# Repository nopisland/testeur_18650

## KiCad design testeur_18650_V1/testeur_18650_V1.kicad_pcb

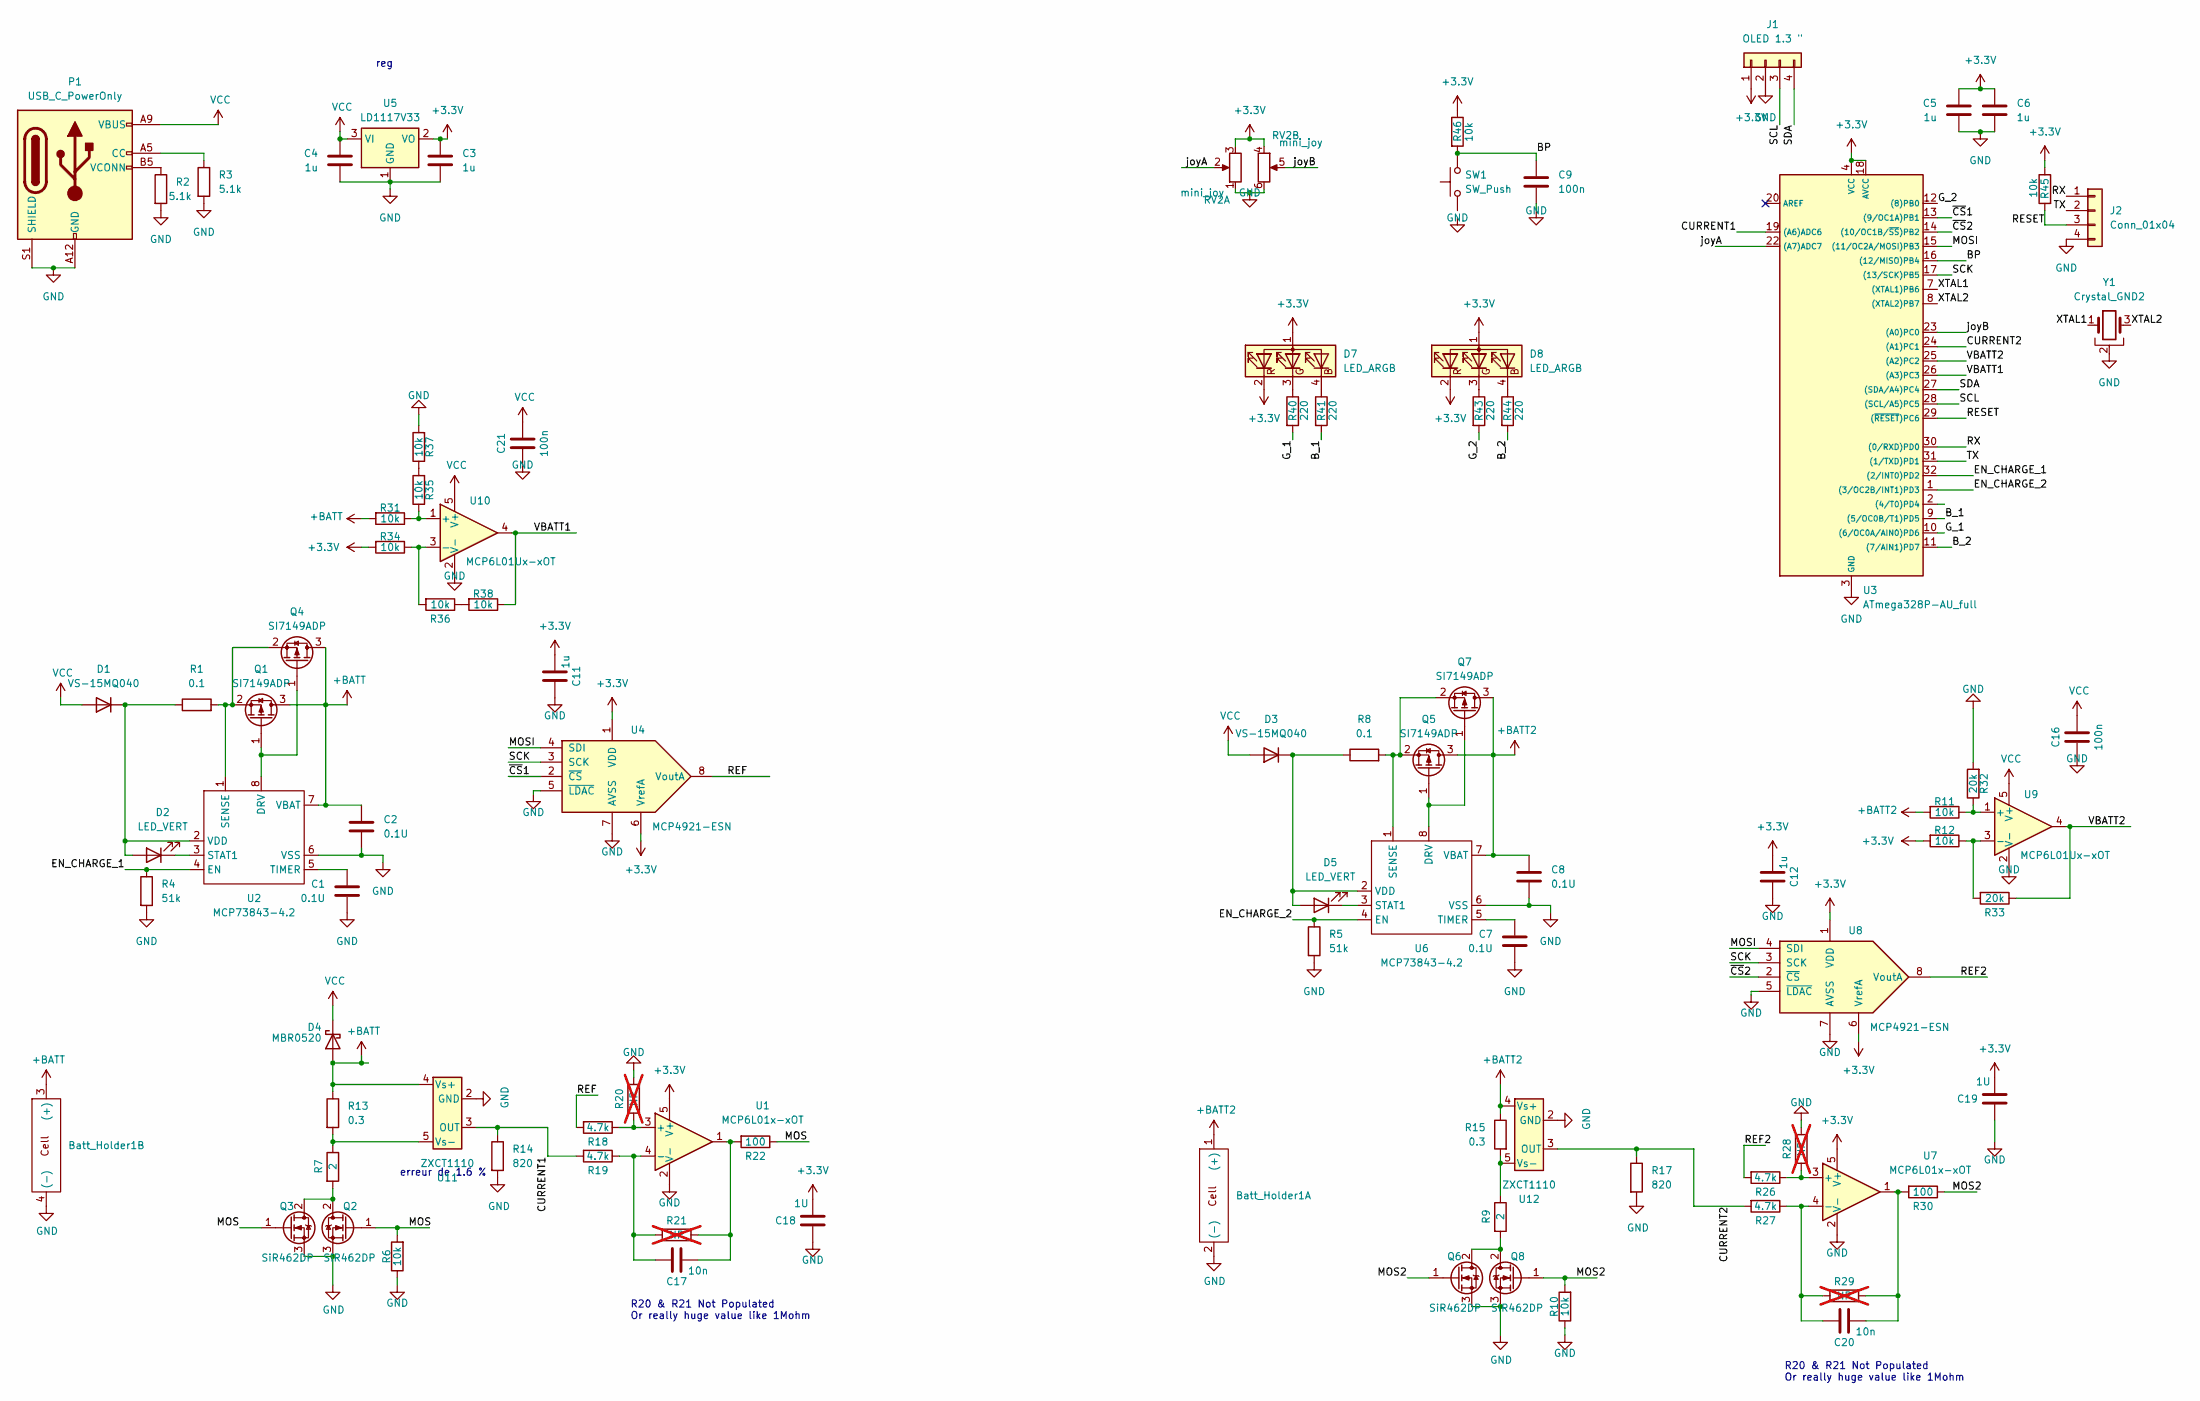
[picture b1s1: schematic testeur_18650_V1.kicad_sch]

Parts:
Batt_Holder1: Cell_holder_18650_2
C1, C2, C7, C8: 0.1U; C_0603_1608Metric
C3, C4, C5, C6, C11, C12: 1u; C_0603_1608Metric
C9, C16, C21: 100n; C_0603_1608Metric
C17, C20: 10n; C_0603_1608Metric
C18, C19: 1U; C_0603_1608Metric
D1, D3: VS-15MQ040; D_SMA
D2, D5: LED_VERT; LED_0603_1608Metric
D4: MBR0520; D_SOD-123
D7, D8: LED_ARGB; LED_ASMB-KTF0-0A306
J1: OLED 1.3 "; OLED_1.3inch
J2: Conn_01x04; PinHeader_1x04_P2.54mm_Vertical
P1: USB_C_PowerOnly; USB_C_Receptacle_GCT_USB4135-GF-A_6P_TopMnt_Horizontal
Q1, Q4, Q5, Q7: SI7149ADP; PowerPAK_SO8L
Q2, Q3, Q6, Q8: SiR462DP; PowerPAK_SO8L
R1, R8: 0.1; R_1206_3216Metric
R2, R3: 5.1k; R_0603_1608Metric
R4, R5: 51k; R_0603_1608Metric
R6, R10, R11, R12, R31, R34, R35, R36, R37, R38, R45, R46: 10k; R_0603_1608Metric
R7, R9: 2; Resistor_RH25
R13, R15: 0.3; R_1206_3216Metric
R14, R17: 820; R_0603_1608Metric
R18, R19, R26, R27: 4.7k; R_0603_1608Metric
R20, R21, R28, R29: NP; R_0603_1608Metric; not fitted
R22, R30: 100; R_0603_1608Metric
R32, R33: 20k; R_0603_1608Metric
R40, R41, R43, R44: 220; R_0603_1608Metric
RV2: mini_joy; mini_joy_analog
SW1: SW_Push; BP_Schruter_LSH
U1, U7: MCP6L01x-xOT; SOT-23-5
U2, U6: MCP73843-4.2; MSOP-8_3x3mm_P0.65mm
U3: ATmega328P-AU_full; TQFP32m
U4, U8: MCP4921-ESN; MSOP-8_3x3mm_P0.65mm
U5: LD1117V33; SOT-223-3_TabPin2
U9, U10: MCP6L01Ux-xOT; SOT-23-5
U11, U12: ZXCT1110; SOT-23-5
Y1: Crystal_GND2; osc_CSTNE

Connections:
+3.3V: C3.1, C5.1, C6.1, C11.1, C12.1, C18.1, C19.1, D7.1 (A), D7.2 (RK), D8.1 (A), D8.2 (RK), J1.1, R12.2, R34.2, R45.1, R46.1, RV2.3, RV2.4, U1.5 (V+), U3.4 (VCC), U3.6 (VCC), U3.18 (AVCC), U4.1 (VDD), U4.6 (VrefA), U5.2 (VO), U7.5 (V+), U8.1 (VDD), U8.6 (VrefA)
+BATT: Batt_Holder1.3 ((+)), C2.1, D4.2 (A), Q1.3 (D), Q4.3 (D), R13.1, R31.2, U2.7 (VBAT), U11.4 (Vs+)
+BATT2: Batt_Holder1.1 ((+)), C8.1, Q5.3 (D), Q7.3 (D), R11.2, R15.1, U6.7 (VBAT), U12.4 (Vs+)
/BP: C9.1, R46.2, SW1.2 (2_2), U3.16 ((12/MISO)PB4)
/B_1: R41.2, U3.9 ((5/OC0B/T1)PD5)
/B_2: R44.2, U3.11 ((7/AIN1)PD7)
/CURRENT1: R14.1, R19.2, U3.19 ((A6)ADC6), U11.3 (OUT)
/CURRENT2: R17.1, R27.2, U3.24 ((A1)PC1), U12.3 (OUT)
/EN_CHARGE_1: R4.1, U2.4 (EN), U3.32 ((2/INT0)PD2)
/EN_CHARGE_2: R5.1, U3.1 ((3/OC2B/INT1)PD3), U6.4 (EN)
/G_1: R40.2, U3.10 ((6/OC0A/AIN0)PD6)
/G_2: R43.2, U3.12 ((8)PB0)
/MOS: Q2.1 (G), Q3.1 (G), R6.2, R22.1
/MOS2: Q6.1 (G), Q8.1 (G), R10.2, R30.1
/MOSI: U3.15 ((11/OC2A/MOSI)PB3), U4.4 (SDI), U8.4 (SDI)
/REF: R18.2, U4.8 (VoutA)
/REF2: R26.2, U8.8 (VoutA)
/RESET: J2.3, R45.2, U3.29 ((~RESET)PC6)
/RX: J2.1, U3.30 ((0/RXD)PD0)
/SCK: U3.17 ((13/SCK)PB5), U4.3 (SCK), U8.3 (SCK)
/SCL: J1.3, U3.28 ((SCL/A5)PC5)
/SDA: J1.4, U3.27 ((SDA/A4)PC4)
/TX: J2.2, U3.31 ((1/TXD)PD1)
/VBATT1: R38.1, U3.26 ((A3)PC3), U10.4
/VBATT2: R33.1, U3.25 ((A2)PC2), U9.4
/XTAL1: U3.7 ((XTAL1)PB6), Y1.1
/XTAL2: U3.8 ((XTAL2)PB7), Y1.3
/joyA: RV2.2, U3.22 ((A7)ADC7)
/joyB: RV2.5, U3.23 ((A0)PC0)
/~CS1: U3.13 ((9/OC1A)PB1), U4.2 (~CS)
/~CS2: U3.14 ((10/OC1B/~SS)PB2), U8.2 (~CS)
GND: Batt_Holder1.2 ((-)), Batt_Holder1.4 ((-)), C1.2, C2.2, C3.2, C4.2, C5.2, C6.2, C7.2, C8.2, C9.2, C11.2, C12.2, C16.1, C18.2, C19.2, C21.1, J1.2, J2.4, P1.A12 (GND), P1.B12 (GND), P1.S1 (SHIELD), Q2.3 (S), Q3.3 (S), Q6.3 (S), Q8.3 (S), R2.2, R3.2, R4.2, R5.2, R6.1, R10.1, R14.2, R17.2, R20.2, R28.2, R32.2, R37.2, RV2.1, RV2.6, U1.2 (V-), U2.6 (VSS), U3.3 (GND), U3.5 (GND), U3.21 (GND), U4.5 (~LDAC), U4.7 (AVSS), U5.1 (GND), U6.6 (VSS), U7.2 (V-), U8.5 (~LDAC), U8.7 (AVSS), U9.2 (V-), U10.2 (V-), U11.2 (GND), U12.2 (GND), Y1.2
unnamed: C17.1, R21.2, R22.2, U1.1
unnamed: C20.1, R29.2, R30.2, U7.1
unnamed: D1.1 (K), D2.2 (A), R1.1, U2.2 (VDD)
unnamed: D2.1 (K), U2.3 (STAT1)
unnamed: D3.1 (K), D5.2 (A), R8.1, U6.2 (VDD)
unnamed: D5.1 (K), U6.3 (STAT1)
unnamed: D7.4 (BK), R41.1
unnamed: D7.3 (GK), R40.1
unnamed: D8.4 (BK), R44.1
unnamed: D8.3 (GK), R43.1
unnamed: P1.A5 (CC), R3.1
unnamed: P1.B5 (VCONN), R2.1
unnamed: Q1.1 (G), Q4.1 (G), U2.8 (DRV)
unnamed: Q1.2 (S), Q4.2 (S), R1.2, U2.1 (SENSE)
unnamed: Q2.2 (D), Q3.2 (D), R7.2
unnamed: Q5.1 (G), Q7.1 (G), U6.8 (DRV)
unnamed: Q5.2 (S), Q7.2 (S), R8.2, U6.1 (SENSE)
unnamed: Q6.2 (D), Q8.2 (D), R9.2
unnamed: R35.2, R37.1
unnamed: R36.1, R38.2
unnamed: R18.1, R20.1, U1.3 (+)
unnamed: C17.2, R19.1, R21.1, U1.4 (-)
unnamed: C1.1, U2.5 (TIMER)
unnamed: C7.1, U6.5 (TIMER)
unnamed: R26.1, R28.1, U7.3 (+)
unnamed: C20.2, R27.1, R29.1, U7.4 (-)
unnamed: R11.1, R32.1, U9.1 (+)
unnamed: R12.1, R33.2, U9.3 (-)
unnamed: R31.1, R35.1, U10.1 (+)
unnamed: R34.1, R36.2, U10.3 (-)
unnamed: R7.1, R13.2, U11.5 (Vs-)
unnamed: R9.1, R15.2, U12.5 (Vs-)
VCC: C4.1, C16.2, C21.2, D1.2 (A), D3.2 (A), D4.1 (K), P1.A9 (VBUS), P1.B9 (VBUS), U5.3 (VI), U9.5 (V+), U10.5 (V+)

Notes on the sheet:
R20 & R21 Not Populated Or really huge value like 1Mohm
erreur de 1.6 %
reg

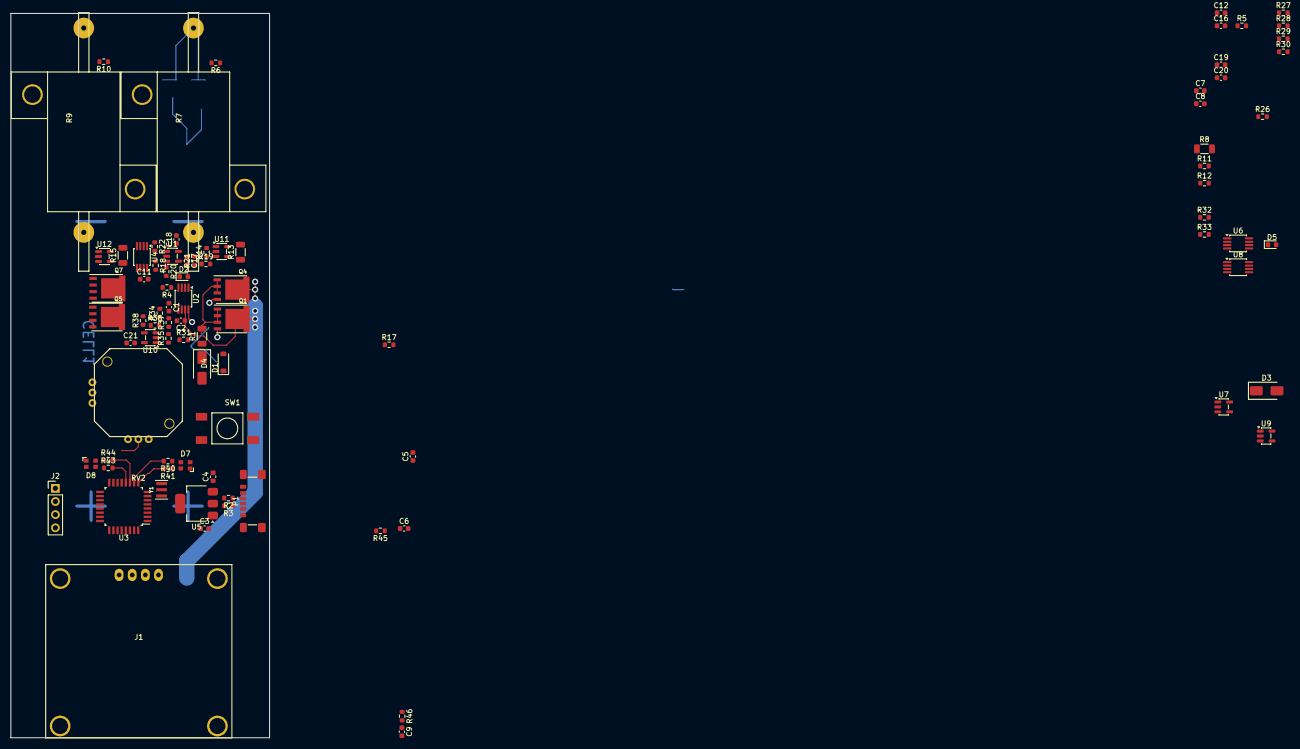
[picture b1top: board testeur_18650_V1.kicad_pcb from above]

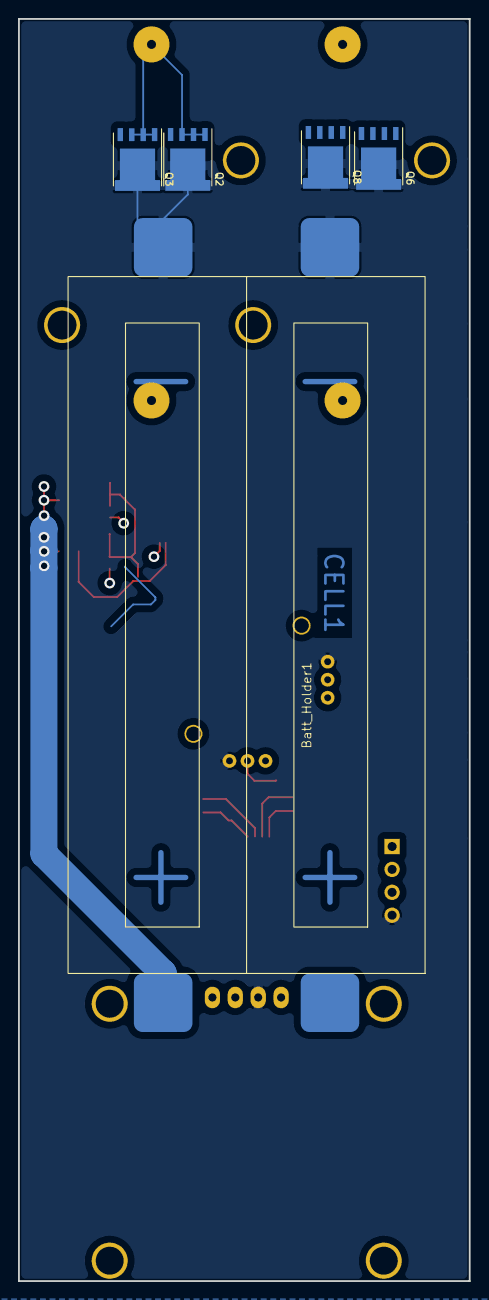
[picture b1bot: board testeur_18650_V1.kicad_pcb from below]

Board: 2 copper layers, 50.0 x 140.0 mm, 91 parts (5 on the bottom side), 65 nets.
